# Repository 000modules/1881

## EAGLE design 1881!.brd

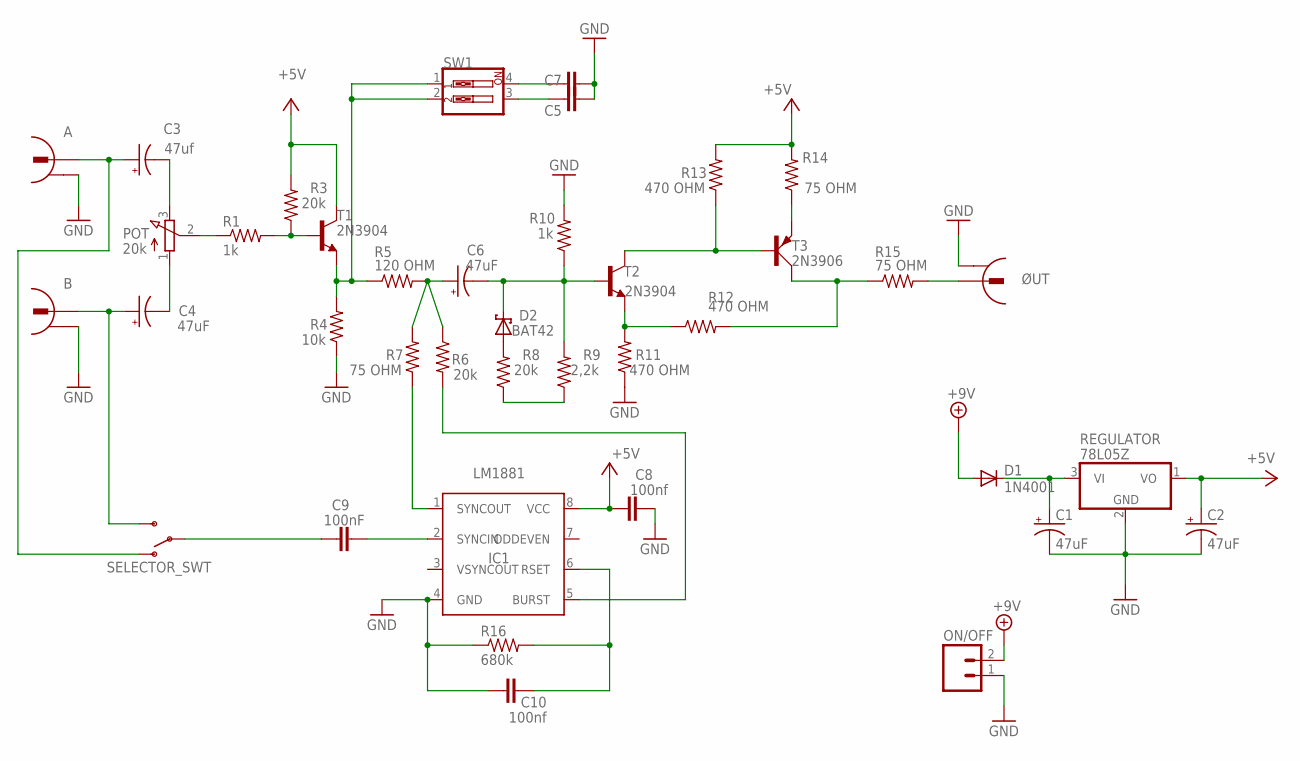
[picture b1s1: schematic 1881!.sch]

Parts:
A: 736880-49
B: 736880-49
C1, C2, C4, C6: 47uF; CPOL-RADIAL-10UF-25V
C3: 47uf; CPOL-RADIAL-10UF-25V
C5, C7: CAPPTH2; CAP-PTH-SMALL2
C8, C10: 100nf; CAP-PTH-SMALL2
C9: 100nF; CAP-PTH-SMALL2
D1: 1N4001; DO35-7
D2: BAT42; DO35-10
IC1: LM1881; DIL08
ON/OFF: M02POLAR_LOCK; MOLEX-1X2_LOCK
POT: 20k; 3RP/1610N
R1, R10: 1k; 1/6W-RES
R3, R6, R8: 20k; 1/6W-RES
R4: 10k; 1/6W-RES
R5: 120 OHM; 1/6W-RES
R7, R14, R15: 75 OHM; 1/6W-RES
R9: 2,2k; 1/6W-RES
R11, R12, R13: 470 OHM; 1/6W-RES
R16: 680k; 1/6W-RES
REGULATOR: 78L05Z; TO92
SELECTOR_SWT: SWITCH-SPSTPTH; SWITCH-SPDT
SW1: SW_DIP-2; DIPSWITCH-02
T1, T2: 2N3904; TO92
T3: 2N3906; TO92D
ØUT: 736880-49

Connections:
+5V: C2.1 (+), C8.1, IC1.8 (VCC), R3.2, R13.2, R14.2, REGULATOR.1 (VO), T1.1 (C)
+9V: D1.A, ON/OFF.2
GND: A.2, B.2, C1.2 (-), C2.2 (-), C5.2, C7.2, C8.2, C10.1, IC1.4 (GND), ON/OFF.1, R4.1, R10.2, R11.1, R16.1, REGULATOR.2 (GND), ØUT.2
unnamed: C1.1 (+), D1.C, REGULATOR.3 (VI)
unnamed: B.1, C4.1 (+), SELECTOR_SWT.3 (S)
unnamed: A.1, C3.1 (+), SELECTOR_SWT.1 (O)
unnamed: C3.2 (-), POT.3 (E)
unnamed: C4.2 (-), POT.1 (A)
unnamed: POT.2 (S), R1.1
unnamed: R1.2, R3.1, T1.2 (B)
unnamed: C6.1 (+), R5.2, R6.1, R7.2
unnamed: IC1.1 (SYNCOUT), R7.1
unnamed: D2.A, R8.2
unnamed: C6.2 (-), D2.C, R9.2, R10.1, T2.2 (B)
unnamed: R8.1, R9.1
unnamed: R11.2, R12.1, T2.3 (E)
unnamed: R13.1, T2.1 (C), T3.B
unnamed: R14.1, T3.E
unnamed: R4.2, R5.1, SW1.1, SW1.2, T1.3 (E)
unnamed: R12.2, R15.1, T3.C
unnamed: R15.2, ØUT.1
unnamed: C5.1, SW1.3
unnamed: C7.1, SW1.4
unnamed: IC1.5 (BURST), R6.2
unnamed: C9.2, IC1.2 (SYNCIN)
unnamed: C10.2, IC1.6 (RSET), R16.2
unnamed: C9.1, SELECTOR_SWT.2

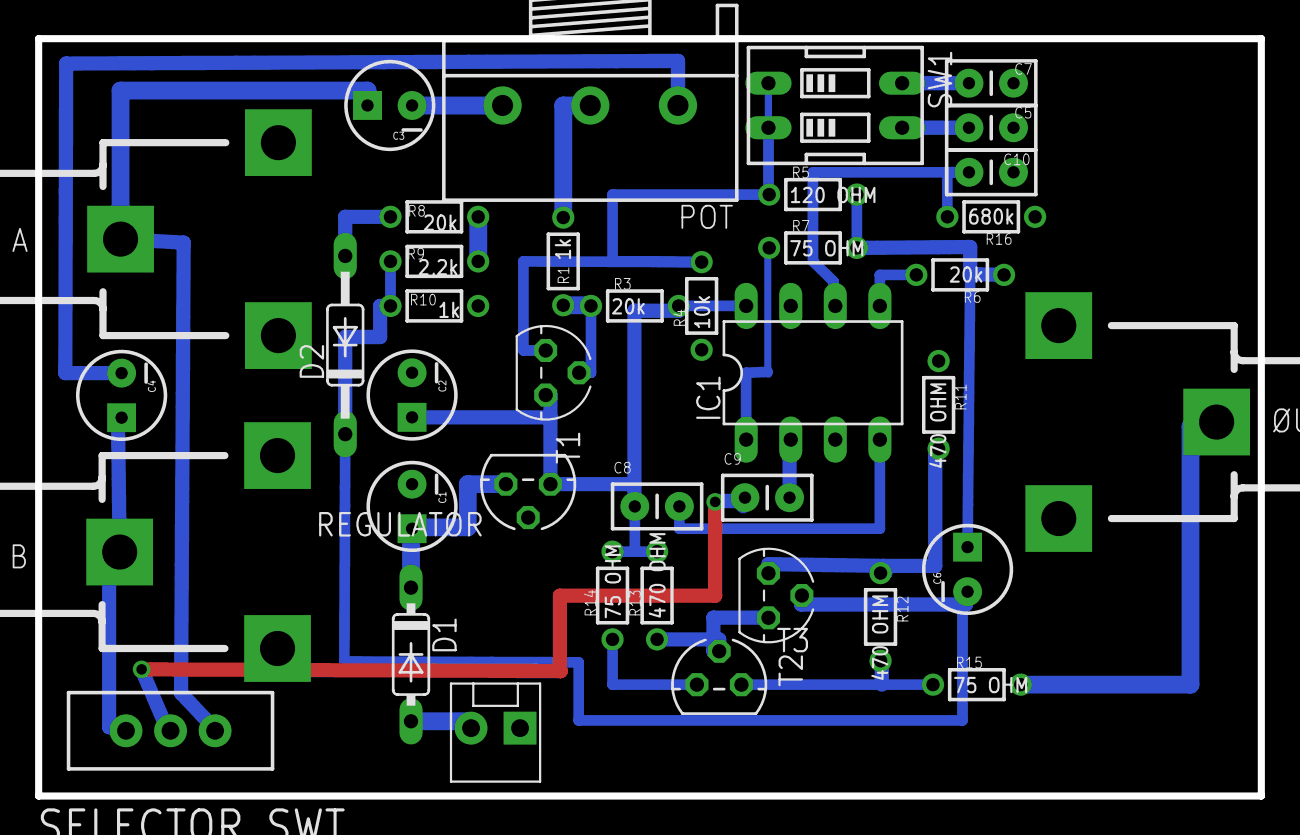
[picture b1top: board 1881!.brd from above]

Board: 2 copper layers, 69.7 x 43.2 mm, 39 parts (0 on the bottom side), 27 nets.

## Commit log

2016-05-27 Git Init 1181
2016-05-27 update all files to push to git

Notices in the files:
parts and their libraries:
SparkFun: Licensing: CC v3.0 Share-Alike You are welcome to use this library for commercial purposes.
